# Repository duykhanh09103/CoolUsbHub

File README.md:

# Very cool usb hub!!
its a 4 port\* usb 3.0 gen1 hub with usb c as a upstream port. It is fully open source and you can built it yourself!!! \
\*1 of its port is for 1gb ethernet

# Key Features
- Built in **1 Gigabit Ethernet** port using [REALTEK RTL8153B](https://www.lcsc.com/product-detail/C2802072.html)
- **2 USB A** and **1 USB C** 3.0 gen 1 downstream port
- **USB C upstream** so you can use **C to C** and **C to USB** cable!!!(with any length you want)
- Very cool art :3

# Why did i make it?
 currently theres literally no usb hub that does usb c 3.0 as upstream without having its cord built in, its bad and if the cord break u either throw it out or destroy the case to repair it.

# How to use it?
 💀 its an usb hub dude, just plug the usb c upstream to a pc and plug peripheral into the usb c and a port 😭

# 3D image 
- With case: (pss, check it out on [onshape](https://cad.onshape.com/documents/b8187d4a30cc3b22176f8391/w/6bf875d6f0e4efab8544a163/e/2b79dfe3cdb89a71b66a7f8a?renderMode=0&uiState=6a1873326ab1afd1b1dcb9ab))

case 2!!

-Without case

# SCHEMATIC
 check out the schematic [here](schematic.pdf) if the image is too blurry

# PCB
 This is a 4 layer pcb made using [Kicad](https://www.kicad.org/), design with attention(😭) to signal intergrity for USB 3 trace! check it out with [kicanvas](https://kicanvas.org/?repo=https%3A%2F%2Fgithub.com%2Fduykhanh09103%2FCoolUsbHub%2Ftree%2Fmain%2Fpcb)!!
 - **Layer 1: signal**

 - **Layer 2: Ground**

 - **Layer 3: Ground**

 - **Layer 4: Signal/Vbus**

# BOM (Bill Of Materials)
> [!IMPORTANT]
> This is the total of the bom including both thing below, do not double count by combining them
> You can leave thing that you already have out of the bom to reduce cost

> [!TIP]
> For any hcer reading this, there is jlc and lcsc cart image in /Image

| Name                    | Amount | Price | Source/Where To Buy | Note                                                     |
|-------------------------|--------|-------|---------------------|----------------------------------------------------------|
| PCB                     | 5      | $12   | JLCPCB              | 4 layer, specify 3313 in stackup(i got white so its 12$) |
| 3D Printed Case         | 2      | $2.74 | JLC3DP              |                                                          |
| PCB Parts               | 2      | $30.86| LCSC                |                                                          |
| Tools and miscellaneous | 1      | $22   |                     |                                                          |
| Shipping                |        | $11   |                     |                                                          |
| Coupon from fallout     |        | -$15  |                     |                                                          |
|                         |        |       |                     |                                                          |
| Total                   |        | $63.6 |                     |                                                          |

## PCB Parts
> [!IMPORTANT]
> This will include how much components you need to use per 1 PCB and the MOQ (minimum of quanity) you can buy. The price will be listed in MOQ. The final price is included everything except shipping.

> [!WARNING]
>  There might be different capacitor/resistor part from production bom because of out of stock

|            Name           | Amount | MOQ |  Price  |         Note         | LCSC Number |
|---------------------------|--------|-----|---------|----------------------|-------------|
| 39pf 50v 0603 Capacitor   | 4      | 100 | $0.48   |                      | C107049     |
| 10uF 10v 0603 Capacitor   | 1      | 20  | $0.53   |                      | C19702      |
| RTL8153B-VB-CG            | 1      | 1   | $3.64   | Ethernet chip (1gb)  | C2802072    |
| 20kΩ 62.5mW 0402 Resistor | 3      | 100 | $0.10   |                      | C93942      |
| 4.7kΩ 63mW 0402 Resistor  | 1      | 100 | $0.44   |                      | C509343     |
| RJ45 Jack                 | 1      | 1   | $2.51   |                      | C54408      |
| HD3SS3220RNHR             | 2      | 1   | $1.9032 | USB TYPE C MUX       | C165155     |
| Type C Receptacle         | 2      | 5   | $1.60   | on sale              | C20883027   |
| GL3510-OSY52              | 1      | 1   | $1.46   | USB HUB              | C7501408    |
| Type A Receptacle         | 2      | 5   | $0.66   |                      | C2845330    |
| 25MHz 20pf crystal        | 2      | 10  | $0.98   |                      | C13740      |
| 900kΩ 250mW 1206 Resistor | 1      | 10  | $0.63   |                      | C871726     |
| 10kΩ 62.5mW 0402 Resistor | 2      | 100 | $0.27   |                      | C2906861    |
| 1kΩ 62.5mW 0402 Resistor  | 1      | 50  | $0.89   |                      | C852624     |
| 200kΩ 100mW 0603 Resistor | 2      | 100 | $0.22   | on sale              | C2907009    |
| 100nF 50V 0603 Capacitor  | 31     | 50  | $0.92   |                      | C282518     |
| 2.49k X   0402 Resistor   | 1      | 100 | 15k VND | I got it from shopee | X           |
|                           |        |     |         |                      |             |
| Total                     |        |     | $19.44  |                      |             |

## Tool and miscellaneous
> [!NOTE]
> If you have the tool already or wanna do this differently, you do not need to buy these

|        Name       | Amount |  Price |          Source          |
|-------------------|--------|--------|--------------------------|
| Hot air gun       | 1      | $21    | Lazada                   |
| Flux              | 1      | $1     | Shopee                   |
| Pinecil           | 1      | $25.99 | Pinecil official website |
| Solder paste/wire | 1      | $1     | Idk its everywhere       |

# How to build??? (soon 👀)
- Order pcb from jlc/any pcb vendor with gerber.zip inside /pcb/production
- there will be video on building one soon

# Credit
 Shoutout to [@tobycm](https://github.com/tobycm) for being the goat and help me a lot with ts project <3\
 This project use kicad, onshape for designing case and pcb\
 Thanks to [Hackclub](https://hackclub.com/) , especially to people running [Fallout](https://fallout.hackclub.com/) for making this project possible :3

# LICENSE
its [MIT](https://opensource.org/license/mit)!! (basically u can do anything with ts). checkout [LICENSE](LICENSE)

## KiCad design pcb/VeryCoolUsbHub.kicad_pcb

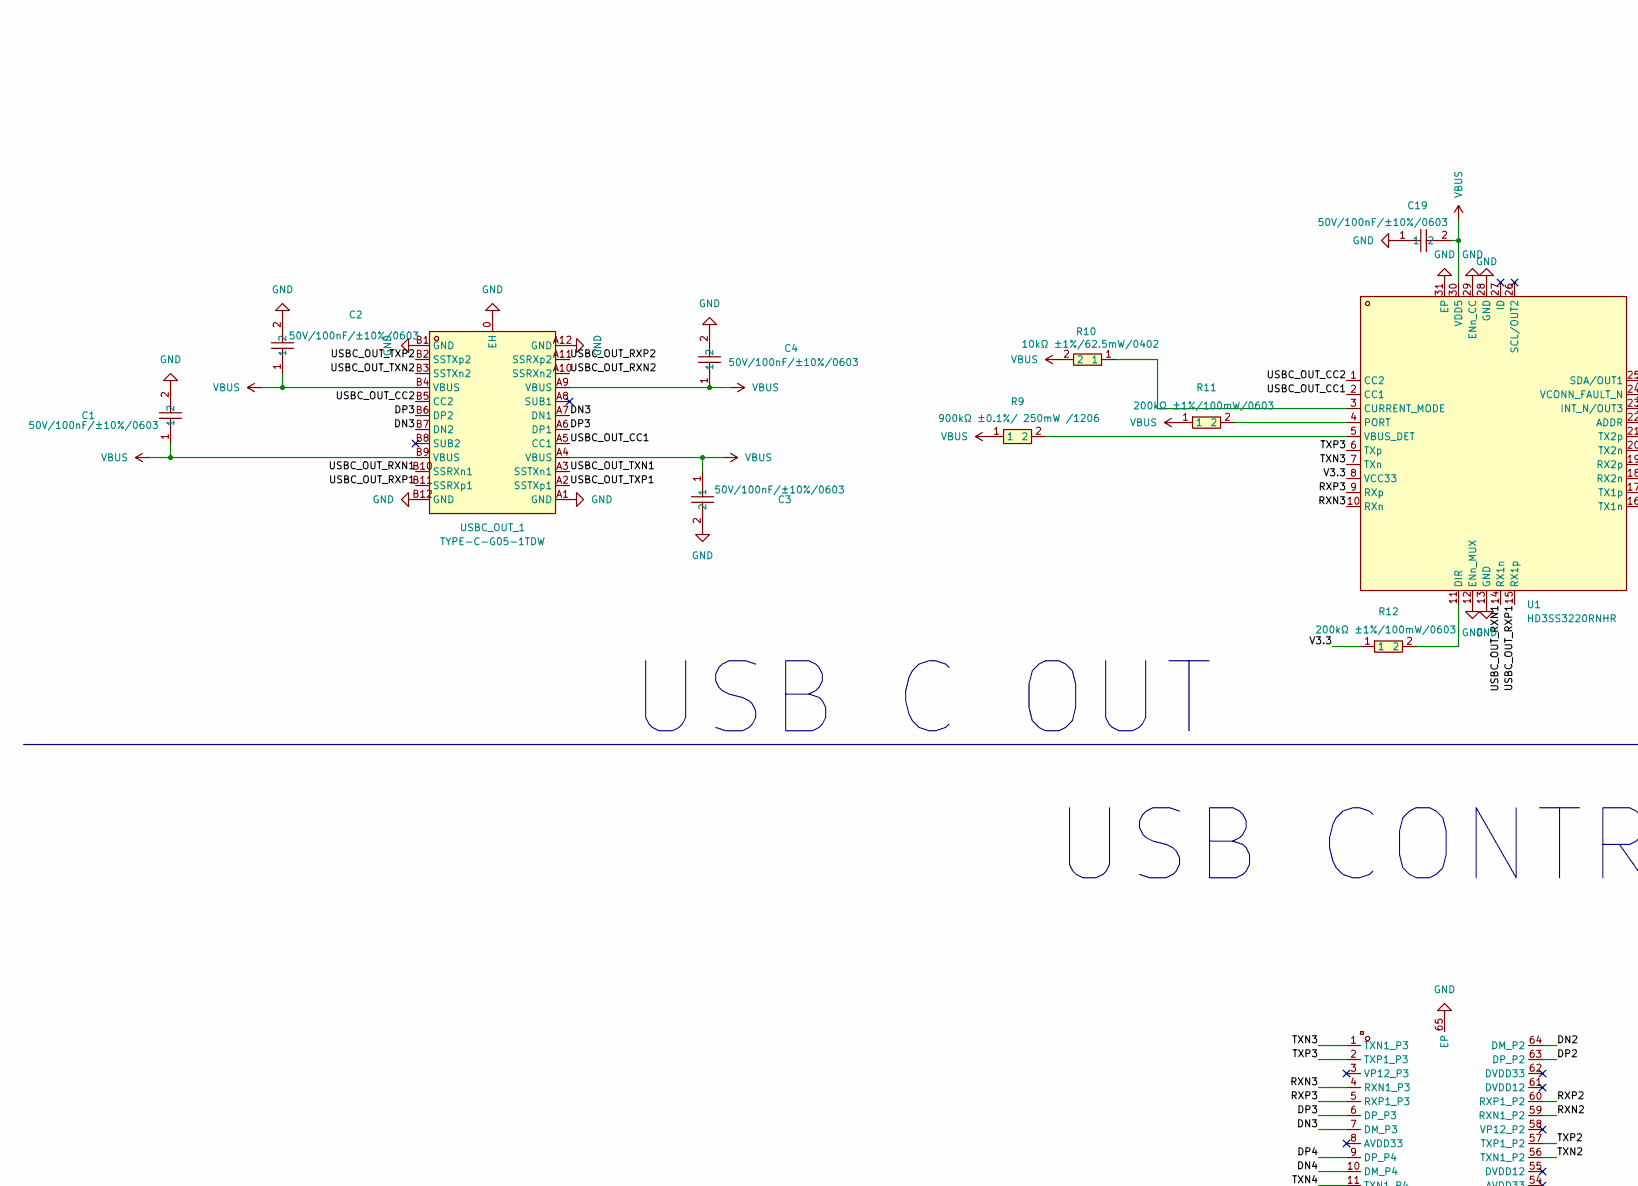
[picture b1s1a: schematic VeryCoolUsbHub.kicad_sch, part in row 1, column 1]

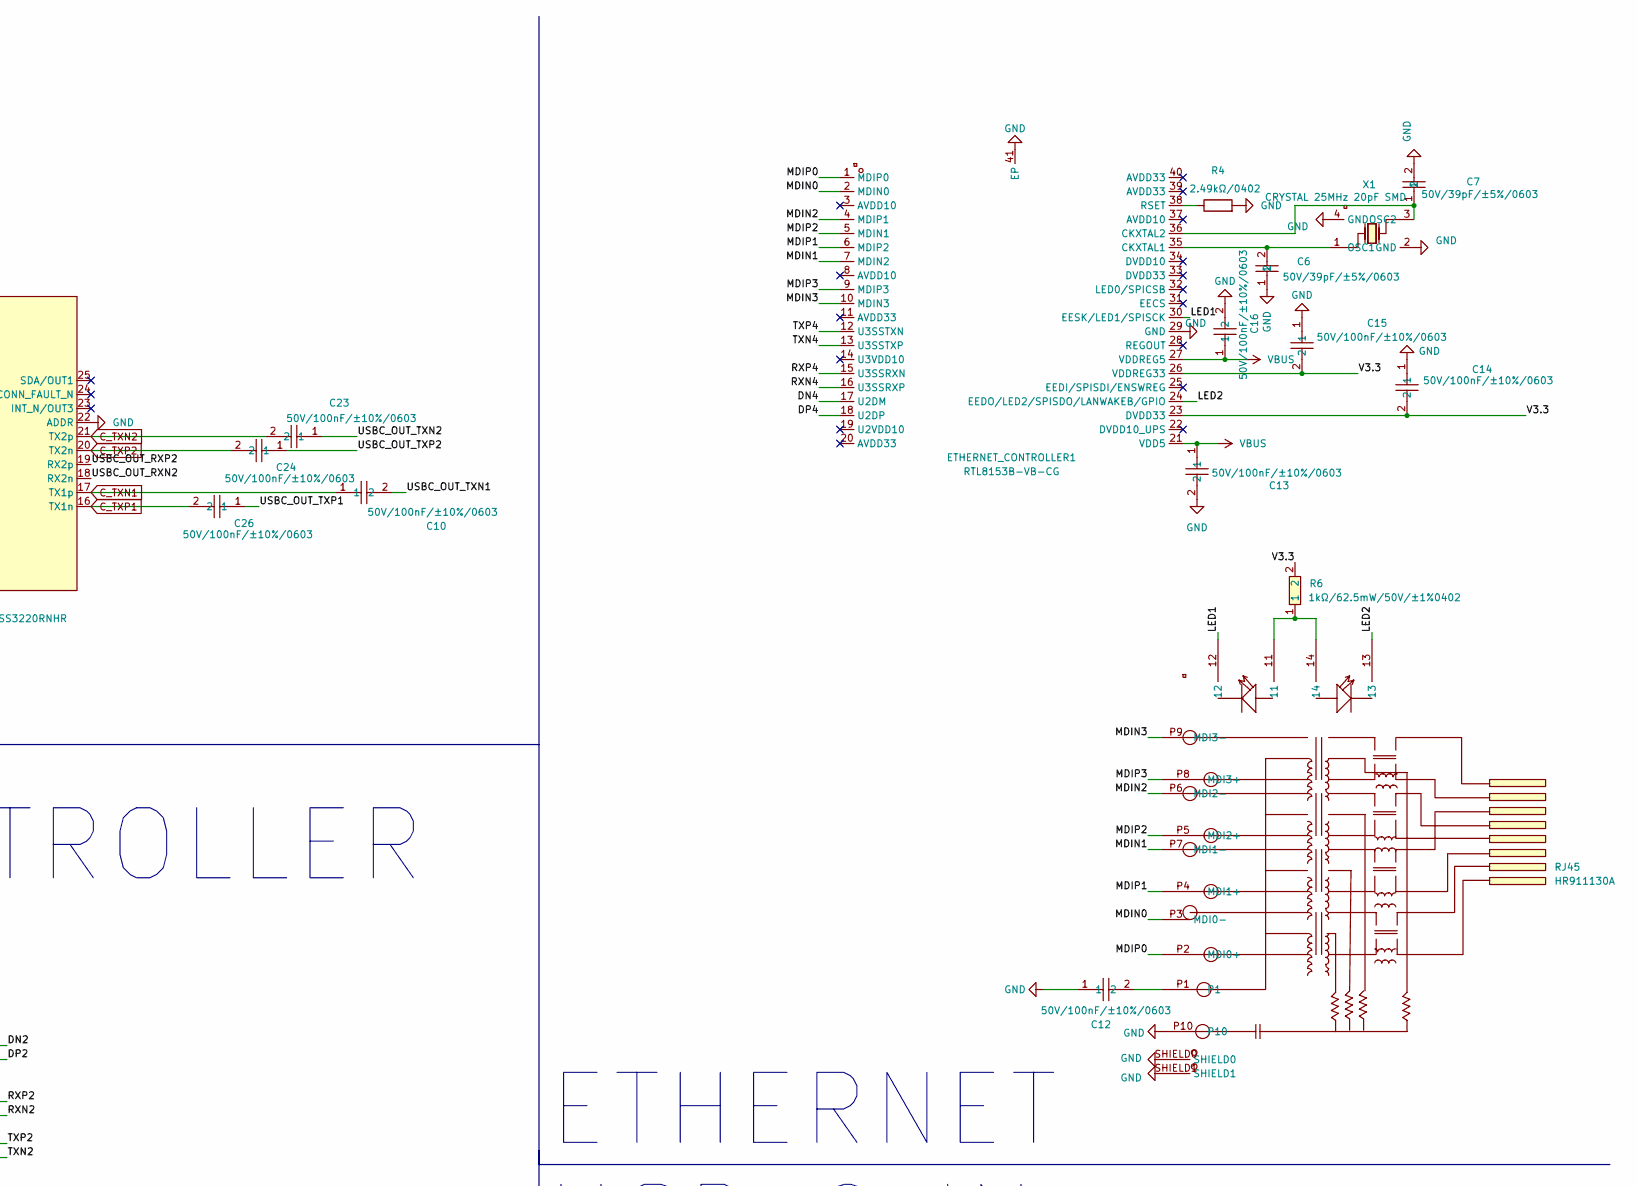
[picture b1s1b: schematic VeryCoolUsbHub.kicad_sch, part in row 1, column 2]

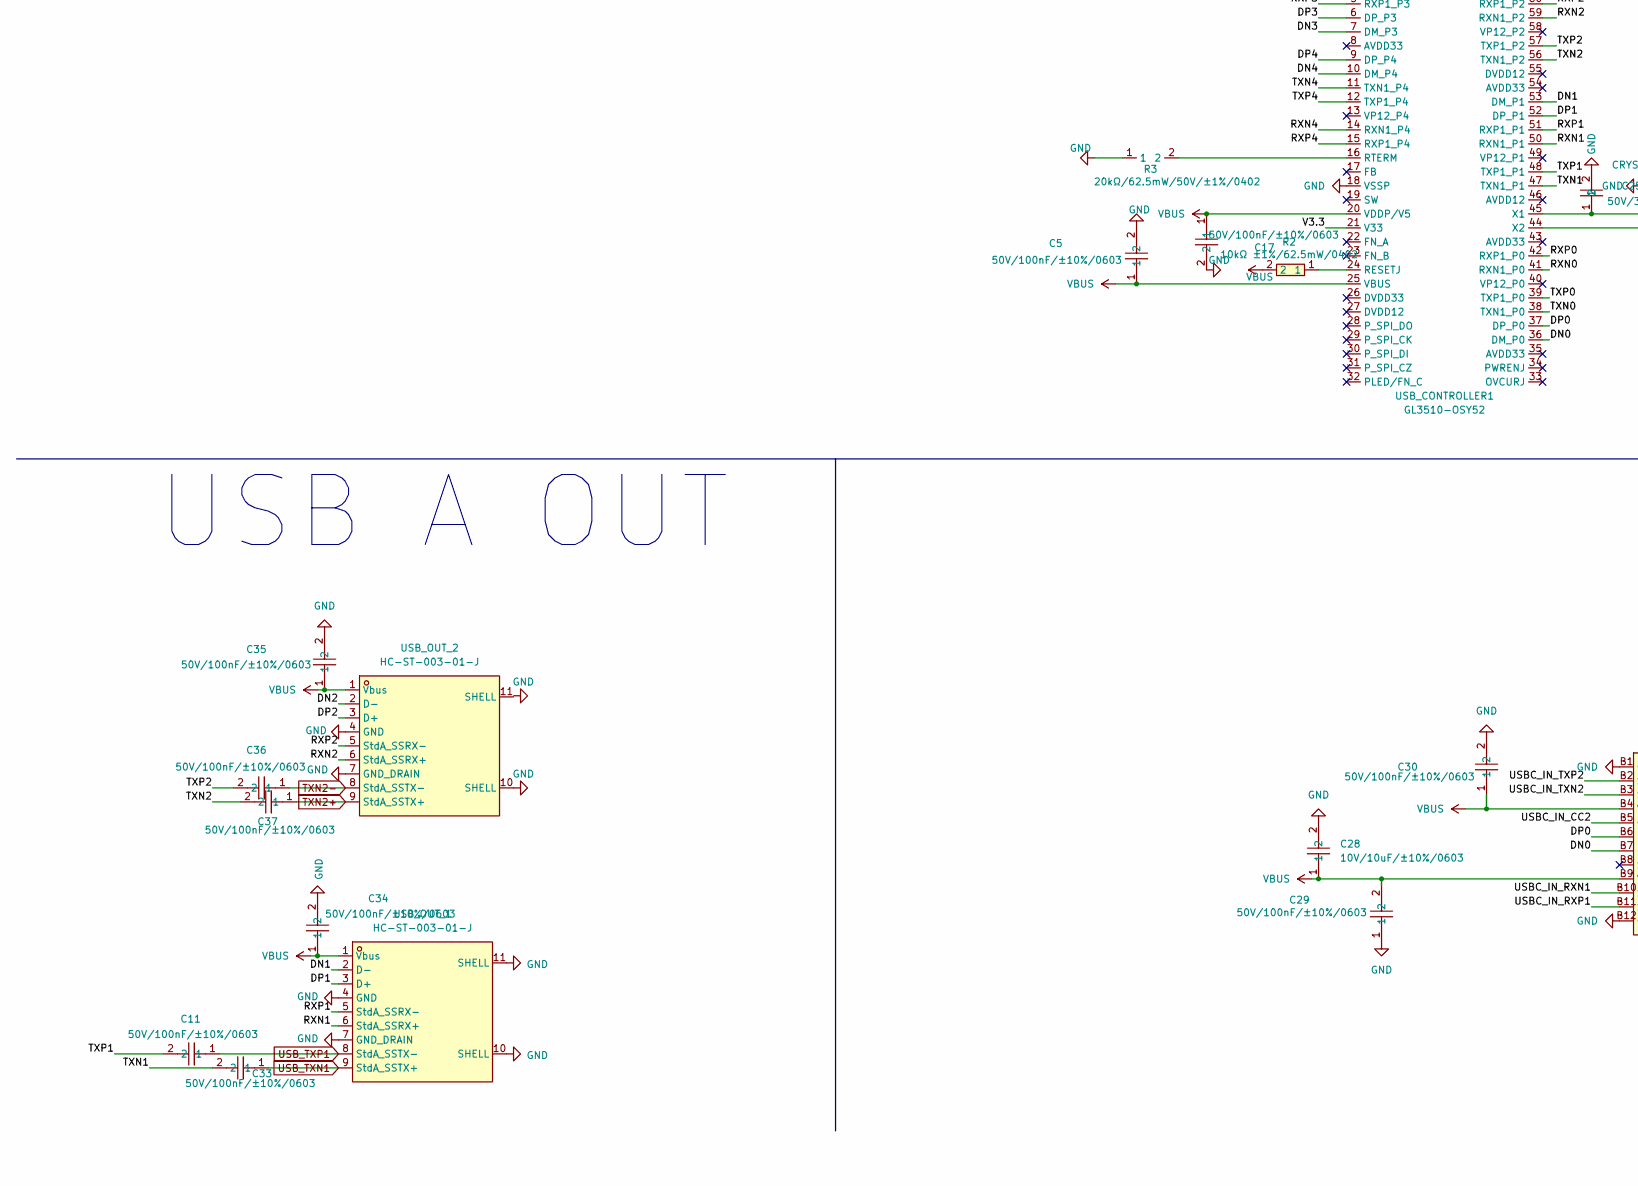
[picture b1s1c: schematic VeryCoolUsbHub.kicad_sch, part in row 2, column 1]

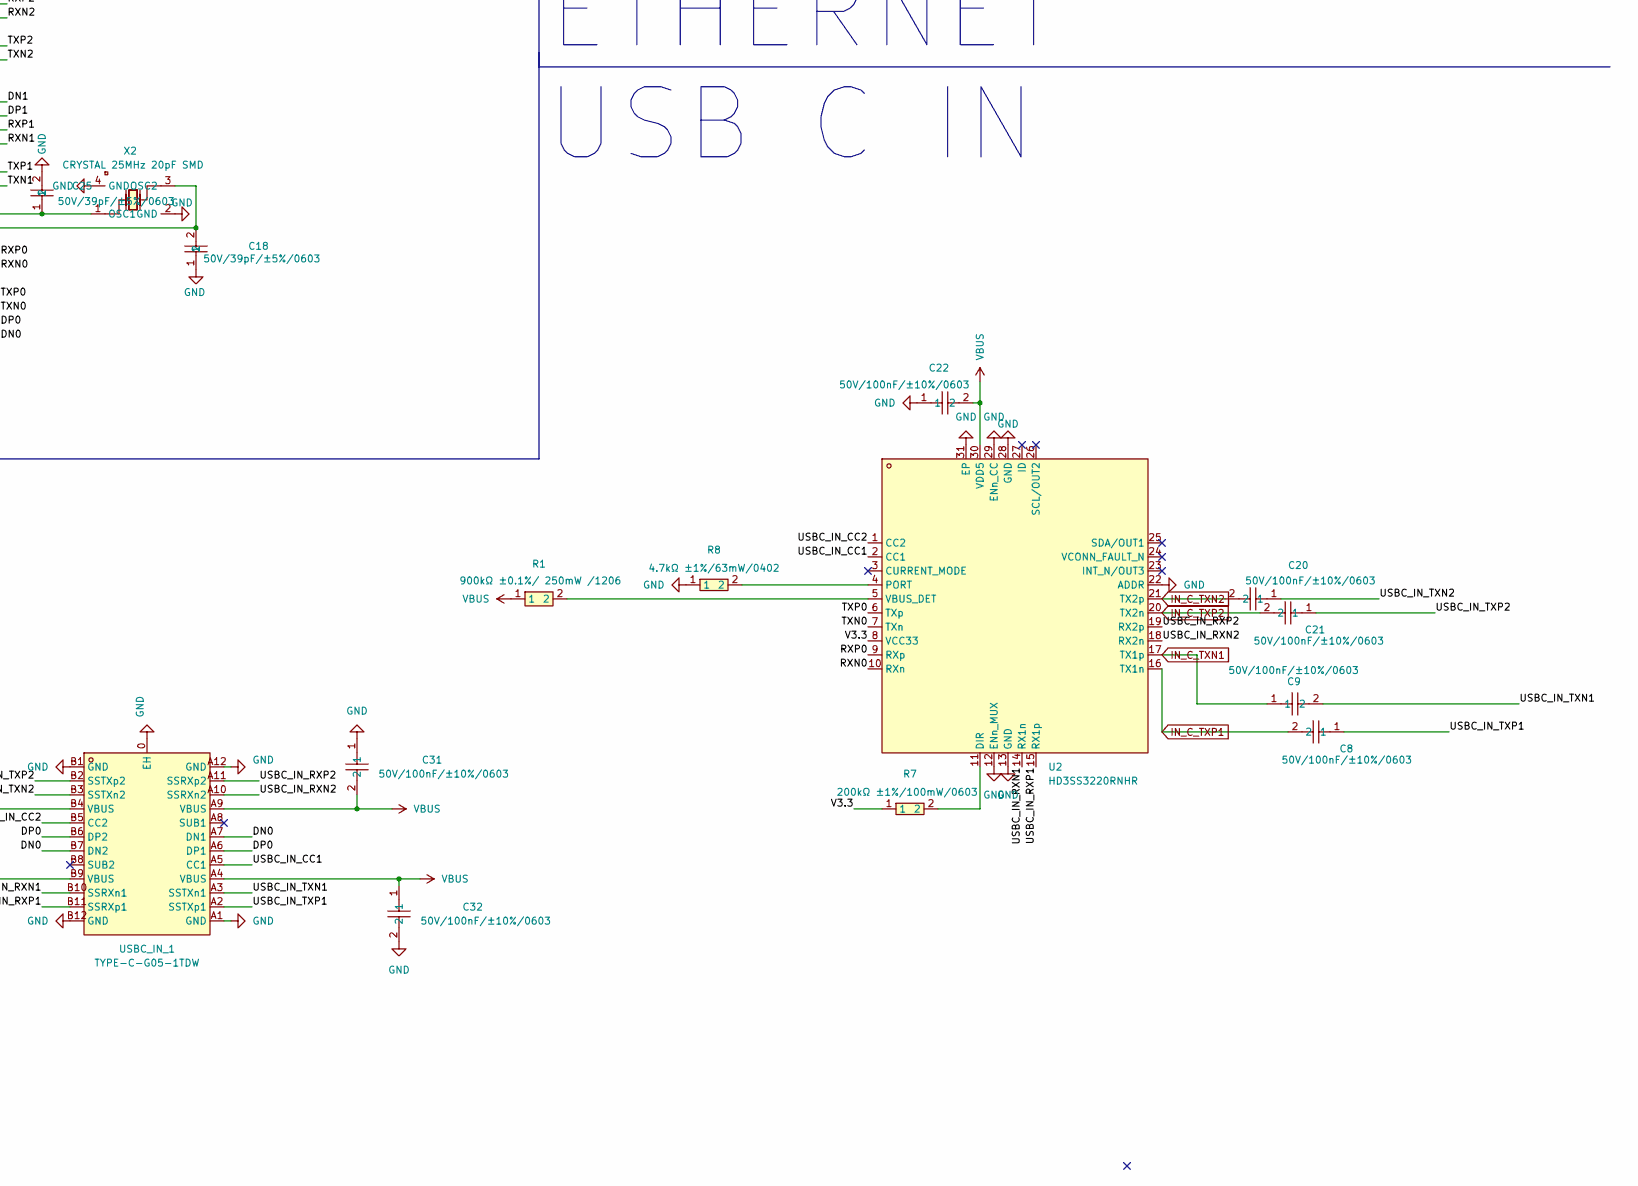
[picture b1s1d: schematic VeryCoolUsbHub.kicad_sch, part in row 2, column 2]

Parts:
C1, C2, C3, C4, C5, C8, C9, C10, C11, C12, C13, C14, C15, C16, C17, C19, C20, C21, C22, C23, C24, C26, C29, C30, C31, C32, C33, C34, C35, C36, C37: CC0603KRX7R9BB104; C0603; LCSC Part C14663
C6, C7, C18, C25: CC0603JRNPO9BN390; C0603; LCSC Part C107049
C28: CL10A106KP8NNNC; C0603; LCSC Part C19702
ETHERNET_CONTROLLER1: RTL8153B-VB-CG; QFN-40_L5.0-W5.0-P0.40-BL-EP3.7; LCSC Part C2802072
R1, R9: RT1206BRE07900KL; R1206; MPN RT1206BRE07900KL; LCSC Part C871499
R2, R10: RC0402FR-0710KL; R0402; MPN RC0402FR-0710KL; LCSC Part C60490
R3: RC0402FR-0720KL; R0402; LCSC Part C93942
R4: R; R_0402_1005Metric
R6: RC0402FR-071KL; R0402; LCSC Part C106235
R7, R11, R12: RC0603FR-07200KL; R0603; MPN RC0603FR-07200KL; LCSC Part C105574
R8: MCR01MZPF4701; R0402; MPN MCR01MZPF4701; LCSC Part C509343
RJ45: HR911130A; RJ45-TH_HR911130A; LCSC Part C54408
U1, U2: HD3SS3220RNHR; WQFN-30_L4.5-W2.5-P0.4-BL-EP; MPN HD3SS3220RNHR; LCSC Part C165155
USBC_IN_1: TYPE-C-G05-1TDW; USB-C-SMD_TYPE-C-G05-1TDW; MPN TYPE-C-G05-1TDW; LCSC Part C20883027
USBC_OUT_1: TYPE-C-G05-1TDW; USB-C-SMD_TYPE-C-G05-1TDW; MPN TYPE-C-G05-1TDW; LCSC Part C20883027
USB_CONTROLLER1: GL3510-OSY52; QFN-64_L8.0-W8.0-P0.40-BL-EP5.4; LCSC Part C7501408
USB_OUT_1, USB_OUT_2: HC-ST-003-01-J; USB-3.0-A-TH_HC-ST-003-01-Z; MPN HC-ST-003-01-J; LCSC Part C2845330
X1, X2: X322525MSB4SI; CRYSTAL-SMD_4P-L3.2-W2.5-BL-2; LCSC Part C13740

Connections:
/DN0: USBC_IN_1.A7 (DN1), USBC_IN_1.B7 (DN2), USB_CONTROLLER1.36 (DM_P0)
/DN1: USB_CONTROLLER1.53 (DM_P1), USB_OUT_1.2 (D-)
/DN2: USB_CONTROLLER1.64 (DM_P2), USB_OUT_2.2 (D-)
/DN3: USBC_OUT_1.A7 (DN1), USBC_OUT_1.B7 (DN2), USB_CONTROLLER1.7 (DM_P3)
/DN4: ETHERNET_CONTROLLER1.17 (U2DM), USB_CONTROLLER1.10 (DM_P4)
/DP0: USBC_IN_1.A6 (DP1), USBC_IN_1.B6 (DP2), USB_CONTROLLER1.37 (DP_P0)
/DP1: USB_CONTROLLER1.52 (DP_P1), USB_OUT_1.3 (D+)
/DP2: USB_CONTROLLER1.63 (DP_P2), USB_OUT_2.3 (D+)
/DP3: USBC_OUT_1.A6 (DP1), USBC_OUT_1.B6 (DP2), USB_CONTROLLER1.6 (DP_P3)
/DP4: ETHERNET_CONTROLLER1.18 (U2DP), USB_CONTROLLER1.9 (DP_P4)
/LED1: ETHERNET_CONTROLLER1.30 (EESK/LED1/SPISCK), RJ45.12
/LED2: ETHERNET_CONTROLLER1.24 (EEDO/LED2/SPISDO/LANWAKEB/GPIO), RJ45.13
/MDIN0: ETHERNET_CONTROLLER1.2 (MDIN0), RJ45.P3 (MDI0-)
/MDIN1: ETHERNET_CONTROLLER1.7 (MDIN2), RJ45.P7 (MDI1-)
/MDIN2: ETHERNET_CONTROLLER1.4 (MDIP1), RJ45.P6 (MDI2-)
/MDIN3: ETHERNET_CONTROLLER1.10 (MDIN3), RJ45.P9 (MDI3-)
/MDIP0: ETHERNET_CONTROLLER1.1 (MDIP0), RJ45.P2 (MDI0+)
/MDIP1: ETHERNET_CONTROLLER1.6 (MDIP2), RJ45.P4 (MDI1+)
/MDIP2: ETHERNET_CONTROLLER1.5 (MDIN1), RJ45.P5 (MDI2+)
/MDIP3: ETHERNET_CONTROLLER1.9 (MDIP3), RJ45.P8 (MDI3+)
/RXN0: U2.10 (RXn), USB_CONTROLLER1.41 (RXN1_P0)
/RXN1: USB_CONTROLLER1.50 (RXN1_P1), USB_OUT_1.6 (StdA_SSRX+)
/RXN2: USB_CONTROLLER1.59 (RXN1_P2), USB_OUT_2.6 (StdA_SSRX+)
/RXN3: U1.10 (RXn), USB_CONTROLLER1.4 (RXN1_P3)
/RXN4: ETHERNET_CONTROLLER1.16 (U3SSRXP), USB_CONTROLLER1.14 (RXN1_P4)
/RXP0: U2.9 (RXp), USB_CONTROLLER1.42 (RXP1_P0)
/RXP1: USB_CONTROLLER1.51 (RXP1_P1), USB_OUT_1.5 (StdA_SSRX-)
/RXP2: USB_CONTROLLER1.60 (RXP1_P2), USB_OUT_2.5 (StdA_SSRX-)
/RXP3: U1.9 (RXp), USB_CONTROLLER1.5 (RXP1_P3)
/RXP4: ETHERNET_CONTROLLER1.15 (U3SSRXN), USB_CONTROLLER1.15 (RXP1_P4)
/TXN0: U2.7 (TXn), USB_CONTROLLER1.38 (TXN1_P0)
/TXN1: C33.2, USB_CONTROLLER1.47 (TXN1_P1)
/TXN2: C37.2, USB_CONTROLLER1.56 (TXN1_P2)
/TXN3: U1.7 (TXn), USB_CONTROLLER1.1 (TXN1_P3)
/TXN4: ETHERNET_CONTROLLER1.13 (U3SSTXP), USB_CONTROLLER1.11 (TXN1_P4)
/TXP0: U2.6 (TXp), USB_CONTROLLER1.39 (TXP1_P0)
/TXP1: C11.2, USB_CONTROLLER1.48 (TXP1_P1)
/TXP2: C36.2, USB_CONTROLLER1.57 (TXP1_P2)
/TXP3: U1.6 (TXp), USB_CONTROLLER1.2 (TXP1_P3)
/TXP4: ETHERNET_CONTROLLER1.12 (U3SSTXN), USB_CONTROLLER1.12 (TXP1_P4)
/USBC_IN_CC1: U2.2 (CC1), USBC_IN_1.A5 (CC1)
/USBC_IN_CC2: U2.1 (CC2), USBC_IN_1.B5 (CC2)
/USBC_IN_RXN1: U2.14 (RX1n), USBC_IN_1.B10 (SSRXn1)
/USBC_IN_RXN2: U2.18 (RX2n), USBC_IN_1.A10 (SSRXn2)
/USBC_IN_RXP1: U2.15 (RX1p), USBC_IN_1.B11 (SSRXp1)
/USBC_IN_RXP2: U2.19 (RX2p), USBC_IN_1.A11 (SSRXp2)
/USBC_IN_TXN1: C9.2, USBC_IN_1.A3 (SSTXn1)
/USBC_IN_TXN2: C20.1, USBC_IN_1.B3 (SSTXn2)
/USBC_IN_TXP1: C8.1, USBC_IN_1.A2 (SSTXp1)
/USBC_IN_TXP2: C21.1, USBC_IN_1.B2 (SSTXp2)
/USBC_OUT_CC1: U1.2 (CC1), USBC_OUT_1.A5 (CC1)
/USBC_OUT_CC2: U1.1 (CC2), USBC_OUT_1.B5 (CC2)
/USBC_OUT_RXN1: U1.14 (RX1n), USBC_OUT_1.B10 (SSRXn1)
/USBC_OUT_RXN2: U1.18 (RX2n), USBC_OUT_1.A10 (SSRXn2)
/USBC_OUT_RXP1: U1.15 (RX1p), USBC_OUT_1.B11 (SSRXp1)
/USBC_OUT_RXP2: U1.19 (RX2p), USBC_OUT_1.A11 (SSRXp2)
/USBC_OUT_TXN1: C10.2, USBC_OUT_1.A3 (SSTXn1)
/USBC_OUT_TXN2: C23.1, USBC_OUT_1.B3 (SSTXn2)
/USBC_OUT_TXP1: C26.1, USBC_OUT_1.A2 (SSTXp1)
/USBC_OUT_TXP2: C24.1, USBC_OUT_1.B2 (SSTXp2)
/V3.3: C14.2, C15.2, ETHERNET_CONTROLLER1.23 (DVDD33), ETHERNET_CONTROLLER1.26 (VDDREG33), R6.2, R7.1, R12.1, U1.8 (VCC33), U2.8 (VCC33), USB_CONTROLLER1.21 (V33)
C_TXN1: C10.1, U1.17 (TX1p)
C_TXN2: C23.2, U1.21 (TX2p)
C_TXP1: C26.2, U1.16 (TX1n)
C_TXP2: C24.2, U1.20 (TX2n)
GND: C1.2, C2.2, C3.2, C4.2, C5.2, C6.1, C7.2, C12.1, C13.2, C14.1, C15.1, C16.2, C17.2, C18.1, C19.1, C22.1, C25.2, C28.2, C29.1, C30.2, C31.1, C32.2, C34.2, C35.2, ETHERNET_CONTROLLER1.29 (GND), ETHERNET_CONTROLLER1.41 (EP), R3.1, R4.2, R8.1, RJ45.P10, RJ45.SHIELD0, RJ45.SHIELD1, U1.12 (ENn_MUX), U1.13 (GND), U1.22 (ADDR), U1.28 (GND), U1.29 (ENn_CC), U1.31 (EP), U2.12 (ENn_MUX), U2.13 (GND), U2.22 (ADDR), U2.28 (GND), U2.29 (ENn_CC), U2.31 (EP), USBC_IN_1.0 (EH), USBC_IN_1.A1 (GND), USBC_IN_1.A12 (GND), USBC_IN_1.B1 (GND), USBC_IN_1.B12 (GND), USBC_OUT_1.0 (EH), USBC_OUT_1.A1 (GND), USBC_OUT_1.A12 (GND), USBC_OUT_1.B1 (GND), USBC_OUT_1.B12 (GND), USB_CONTROLLER1.18 (VSSP), USB_CONTROLLER1.65 (EP), USB_OUT_1.4 (GND), USB_OUT_1.7 (GND_DRAIN), USB_OUT_1.10 (SHELL), USB_OUT_1.11 (SHELL), USB_OUT_2.4 (GND), USB_OUT_2.7 (GND_DRAIN), USB_OUT_2.10 (SHELL), X1.2 (GND), X1.4 (GND), X2.2 (GND), X2.4 (GND)
IN_C_TXN1: C9.1, U2.17 (TX1p)
IN_C_TXN2: C20.2, U2.21 (TX2p)
IN_C_TXP1: C8.2, U2.16 (TX1n)
IN_C_TXP2: C21.2, U2.20 (TX2n)
unnamed: C12.2, RJ45.P1
unnamed: C6.2, ETHERNET_CONTROLLER1.35 (CKXTAL1), X1.1 (OSC1)
unnamed: C7.1, ETHERNET_CONTROLLER1.36 (CKXTAL2), X1.3 (OSC2)
unnamed: ETHERNET_CONTROLLER1.38 (RSET), R4.1
unnamed: R6.1, RJ45.11, RJ45.14
unnamed: R10.1, U1.3 (CURRENT_MODE)
unnamed: R12.2, U1.11 (DIR)
unnamed: R11.2, U1.4 (PORT)
unnamed: R9.2, U1.5 (VBUS_DET)
unnamed: R7.2, U2.11 (DIR)
unnamed: R8.2, U2.4 (PORT)
unnamed: R1.2, U2.5 (VBUS_DET)
unnamed: R2.1, USB_CONTROLLER1.24 (RESETJ)
unnamed: R3.2, USB_CONTROLLER1.16 (RTERM)
unnamed: C25.1, USB_CONTROLLER1.45 (X1), X2.1 (OSC1)
unnamed: C18.2, USB_CONTROLLER1.44 (X2), X2.3 (OSC2)
TXN2+: C37.1, USB_OUT_2.9 (StdA_SSTX+)
TXN2-: C36.1, USB_OUT_2.8 (StdA_SSTX-)
USB_TXN1: C33.1, USB_OUT_1.9 (StdA_SSTX+)
USB_TXP1: C11.1, USB_OUT_1.8 (StdA_SSTX-)
VBUS: C1.1, C2.1, C3.1, C4.1, C5.1, C13.1, C16.1, C17.1, C19.2, C22.2, C28.1, C29.2, C30.1, C31.2, C32.1, C34.1, C35.1, ETHERNET_CONTROLLER1.21 (VDD5), ETHERNET_CONTROLLER1.27 (VDDREG5), R1.1, R2.2, R9.1, R10.2, R11.1, U1.30 (VDD5), U2.30 (VDD5), USBC_IN_1.A4 (VBUS), USBC_IN_1.A9 (VBUS), USBC_IN_1.B4 (VBUS), USBC_IN_1.B9 (VBUS), USBC_OUT_1.A4 (VBUS), USBC_OUT_1.A9 (VBUS), USBC_OUT_1.B4 (VBUS), USBC_OUT_1.B9 (VBUS), USB_CONTROLLER1.20 (VDDP/V5), USB_CONTROLLER1.25 (VBUS), USB_OUT_1.1 (Vbus), USB_OUT_2.1 (Vbus)

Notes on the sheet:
USB A OUT
ETHERNET
USB CONTROLLER
USB C OUT
USB C IN

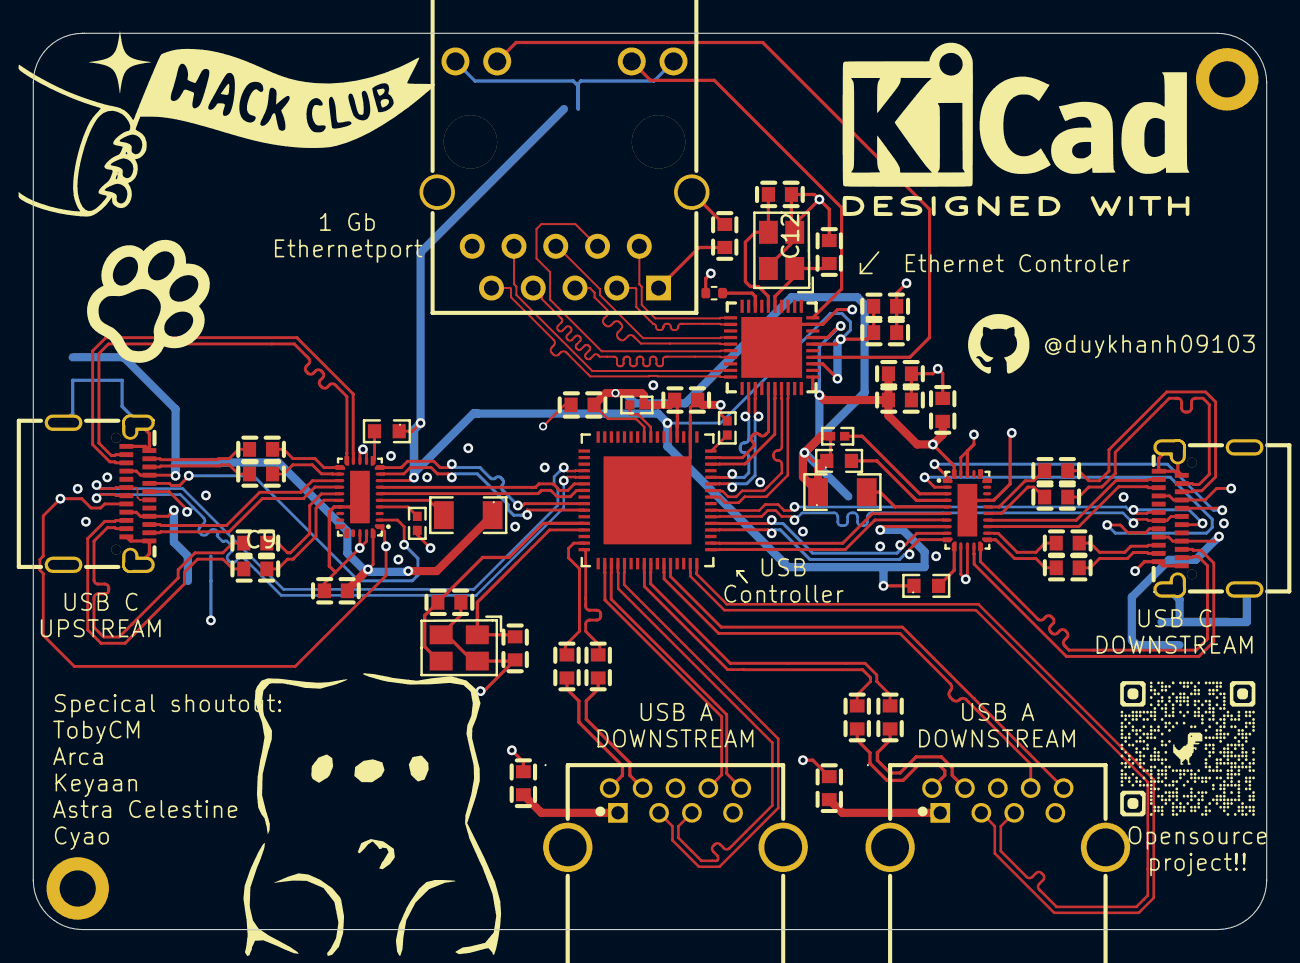
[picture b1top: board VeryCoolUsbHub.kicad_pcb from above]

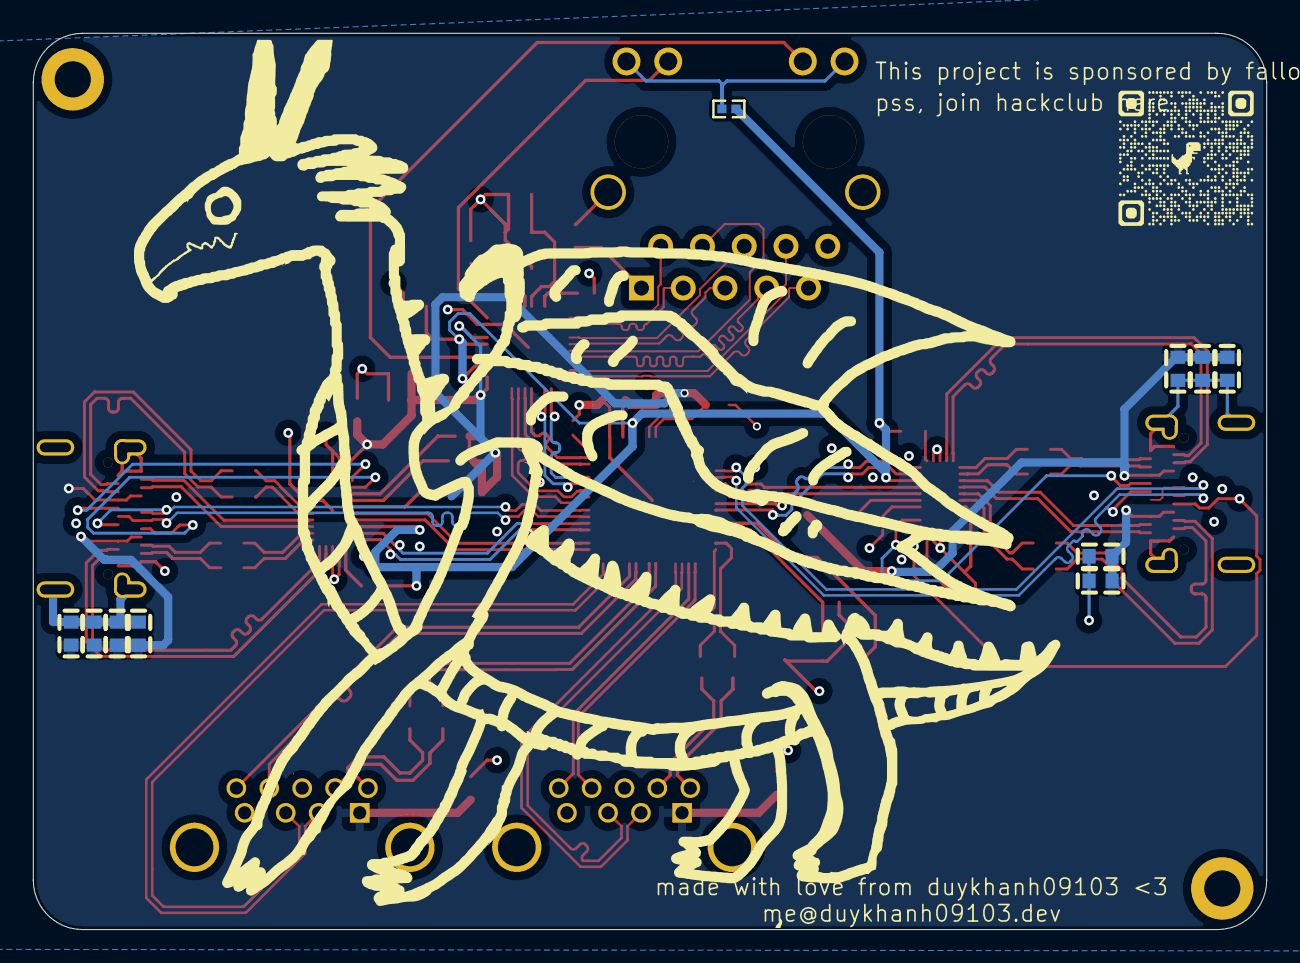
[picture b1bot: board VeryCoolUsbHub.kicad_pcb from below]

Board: 4 copper layers, 75.0 x 54.5 mm, 58 parts (10 on the bottom side), 91 nets.

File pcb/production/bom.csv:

Designator,Footprint,Quantity,Value,LCSC Part #
"C1, C10, C11, C12, C13, C14, C15, C16, C17, C19, C2, C20, C21, C22, C23, C24, C26, C29, C3, C30, C31, C32, C33, C34, C35, C36, C37, C4, C5, C8, C9",C0603,31,CC0603KRX7R9BB104,C14663
"C18, C25, C6, C7",C0603,4,CC0603JRNPO9BN390,C107049
C28,C0603,1,CL10A106KP8NNNC,C19702
ETHERNET_CONTROLLER1,QFN-40_L5.0-W5.0-P0.40-BL-EP3.7,1,RTL8153B-VB-CG,C2802072
"R1, R9",R1206,2,RT1206BRE07900KL,C871499
"R10, R2",R0402,2,RC0402FR-0710KL,C60490
"R11, R12, R7",R0603,3,RC0603FR-07200KL,C105574
R3,R0402,1,RC0402FR-0720KL,C93942
R4,0402,1,R,
R6,R0402,1,RC0402FR-071KL,C106235
R8,R0402,1,MCR01MZPF4701,C509343
RJ45,RJ45-TH_HR911130A,1,HR911130A,C54408
"U1, U2",WQFN-30_L4.5-W2.5-P0.4-BL-EP,2,HD3SS3220RNHR,C165155
"USBC_IN_1, USBC_OUT_1",USB-C-SMD_TYPE-C-G05-1TDW,2,TYPE-C-G05-1TDW,C20883027
USB_CONTROLLER1,QFN-64_L8.0-W8.0-P0.40-BL-EP5.4,1,GL3510-OSY52,C7501408
"USB_OUT_1, USB_OUT_2",USB-3.0-A-TH_HC-ST-003-01-Z,2,HC-ST-003-01-J,C2845330
"X1, X2",CRYSTAL-SMD_4P-L3.2-W2.5-BL-2,2,X322525MSB4SI,C13740

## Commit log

2025-11-26 added jlc file
2025-11-26 changed stuff, add schem for review
2025-11-27 now with everything ig?
2025-11-27 done schem please
2025-11-27 fix kicad fucking up the save folder
2025-11-27 forgor to update schematic pdf
2025-11-27 forgor to link shield to ground
2025-11-27 PLEASE I WANT SLEEP
2025-11-28 do sum pcb
2026-05-19 do a lot of things
2026-05-20 BIG UPDATEEEEEEEEE
2026-05-22 please tell me this is the last time i need to reroute
2026-05-22 oops forgot to save
2026-05-23 LETSGO THIS GONNA BE THE LAST TIME I ROUTE
2026-05-24 maybedone?
2026-05-24 uhhh is this it?
2026-05-24 i think im done with pcb
2026-05-24 add VBUS plane to last layer
2026-05-25 reroute a litlle bit of ethernet port
2026-05-25 screwhole
2026-05-26 added zine
2026-05-26 hell yea? i hope its all
2026-05-26 forgor total
2026-05-26 edit readme.nmd
2026-05-27 fix connector and add case
2026-05-28 change schen
2026-05-28 update a lot of image
2026-05-28 update case
2026-06-04 fix some routing and add assembled case with pcb
2026-06-04 forgor to update
2026-06-04 remove backup folder
2026-06-04 update schematic pdf
2026-06-04 update readme, zine and image
2026-06-14 fixed some signal intergrity problem
2026-06-14 update pcb image base on newest pcb
2026-06-16 fixed signal intergrity stuff
2026-06-17 update Bom in readme
2026-06-17 fixed
2026-06-17 final?
2026-06-17 i forgor 3dp
2026-06-18 update pcb and changed production file to newest
2026-06-18 update zine and pcb image
2026-06-27 fixed small error in pcb
